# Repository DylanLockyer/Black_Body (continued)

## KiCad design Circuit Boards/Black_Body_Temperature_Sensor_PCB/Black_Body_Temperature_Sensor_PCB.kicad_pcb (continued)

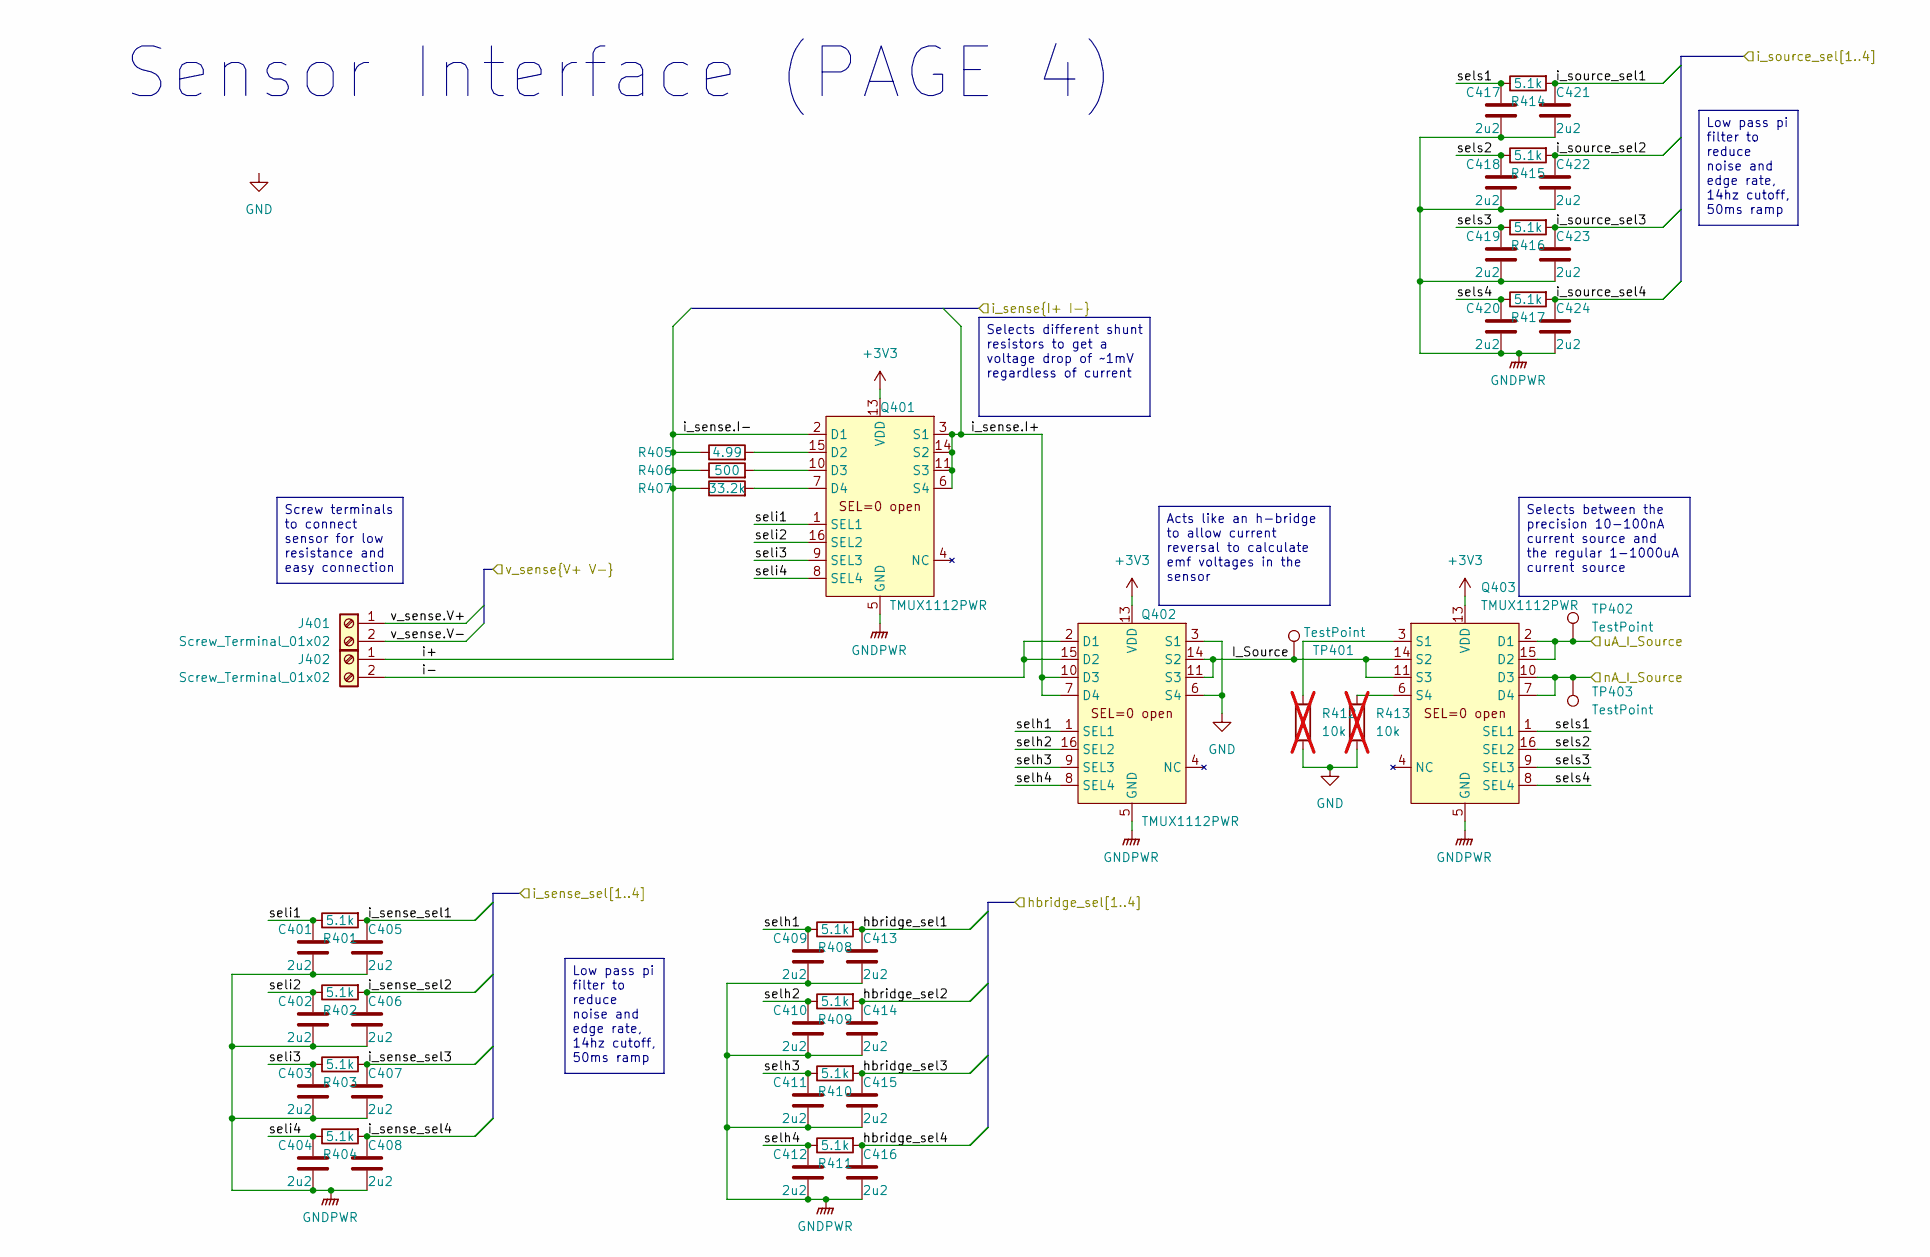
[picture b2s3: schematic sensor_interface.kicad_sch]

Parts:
C401, C402, C403, C404, C405, C406, C407, C408, C409, C410, C411, C412, C413, C414, C415, C416, C417, C418, C419, C420, C421, C422, C423, C424: 2u2; C_0402_1005Metric; MPN GRM155R61E225ME15D
J401, J402: Screw_Terminal_01x02; CUI_TB002-500-02BE; MPN TB002-500-02BE
Q401, Q402, Q403: TMUX1112PWR; TSSOP-16_4.4x5mm_P0.65mm; MPN TMUX1112PWR
R401, R402, R403, R404, R408, R409, R410, R411, R414, R415, R416, R417: 5.1k; R_0402_1005Metric; MPN RT0402BRD075K1L
R405: 4.99; R_0603_1608Metric; MPN RN73C1J4R99BTD
R406: 500; R_0603_1608Metric; MPN ERA-3AEB4990V
R407: 33.2k; R_0603_1608Metric; MPN ERA-3AEB3322V
R412, R413: 10k; R_0603_1608Metric; MPN ERA-3AEB103V; not fitted
TP401, TP402, TP403: TestPoint; TestPoint_Pad_2.0x2.0mm

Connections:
+3V3: Q401.13 (VDD), Q402.13 (VDD), Q403.13 (VDD); also elsewhere on the board
/V&I_sense/i_sense.I+: Q401.3 (S1), Q401.6 (S4), Q401.11 (S3), Q401.14 (S2), Q402.7 (D4), Q402.10 (D3); also elsewhere on the board
/V&I_sense/i_sense.I-: J402.1, Q401.2 (D1), R405.1, R406.1, R407.1; also elsewhere on the board
/V&I_sense/v_sense.V+: J401.1; also elsewhere on the board
/V&I_sense/v_sense.V-: J401.2; also elsewhere on the board
/micrcontroller/hbridge_sel1: C413.1, R408.2; also elsewhere on the board
/micrcontroller/hbridge_sel2: C414.1, R409.2; also elsewhere on the board
/micrcontroller/hbridge_sel3: C415.1, R410.2; also elsewhere on the board
/micrcontroller/hbridge_sel4: C416.1, R411.2; also elsewhere on the board
/micrcontroller/i_sense_sel1: C405.1, R401.2; also elsewhere on the board
/micrcontroller/i_sense_sel2: C406.1, R402.2; also elsewhere on the board
/micrcontroller/i_sense_sel3: C407.1, R403.2; also elsewhere on the board
/micrcontroller/i_sense_sel4: C408.1, R404.2; also elsewhere on the board
/micrcontroller/i_source_sel1: C421.1, R414.2; also elsewhere on the board
/micrcontroller/i_source_sel2: C422.1, R415.2; also elsewhere on the board
/micrcontroller/i_source_sel3: C423.1, R416.2; also elsewhere on the board
/micrcontroller/i_source_sel4: C424.1, R417.2; also elsewhere on the board
/nA_current/nA_I_Source: Q403.7 (D4), Q403.10 (D3), TP403.1 (1_1); also elsewhere on the board
/sensor_interface/I_Source: Q402.11 (S3), Q402.14 (S2), Q403.11 (S3), Q403.14 (S2), TP401.1 (1_1)
/sensor_interface/i-: J402.2, Q402.2 (D1), Q402.15 (D2)
/sensor_interface/selh1: C409.1, Q402.1 (SEL1), R408.1
/sensor_interface/selh2: C410.1, Q402.16 (SEL2), R409.1
/sensor_interface/selh3: C411.1, Q402.9 (SEL3), R410.1
/sensor_interface/selh4: C412.1, Q402.8 (SEL4), R411.1
/sensor_interface/seli1: C401.1, Q401.1 (SEL1), R401.1
/sensor_interface/seli2: C402.1, Q401.16 (SEL2), R402.1
/sensor_interface/seli3: C403.1, Q401.9 (SEL3), R403.1
/sensor_interface/seli4: C404.1, Q401.8 (SEL4), R404.1
/sensor_interface/sels1: C417.1, Q403.1 (SEL1), R414.1
/sensor_interface/sels2: C418.1, Q403.16 (SEL2), R415.1
/sensor_interface/sels3: C419.1, Q403.9 (SEL3), R416.1
/sensor_interface/sels4: C420.1, Q403.8 (SEL4), R417.1
/sensor_interface/uA_I_Source: Q403.2 (D1), Q403.15 (D2), TP402.1 (1_1); also elsewhere on the board
GND: Q402.3 (S1), Q402.6 (S4), R412.2, R413.2; also elsewhere on the board
GNDPWR: C401.2, C402.2, C403.2, C404.2, C405.2, C406.2, C407.2, C408.2, C409.2, C410.2, C411.2, C412.2, C413.2, C414.2, C415.2, C416.2, C417.2, C418.2, C419.2, C420.2, C421.2, C422.2, C423.2, C424.2, Q401.5 (GND), Q402.5 (GND), Q403.5 (GND); also elsewhere on the board
unnamed: Q401.15 (D2), R405.2
unnamed: Q401.10 (D3), R406.2
unnamed: Q401.7 (D4), R407.2
unnamed: Q403.3 (S1), R412.1
unnamed: Q403.6 (S4), R413.1

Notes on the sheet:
Sensor Interface (PAGE 4)
Low pass pi filter to reduce noise and edge rate, 14hz cutoff, 50ms ramp
Acts like an h-bridge to allow current reversal to calculate emf voltages in the sensor
Selects different shunt resistors to get a voltage drop of ~1mV regardless of current
Screw terminals to connect sensor for low resistance and easy connection
Selects between the precision 10-100nA current source and the regular 1-1000uA current source

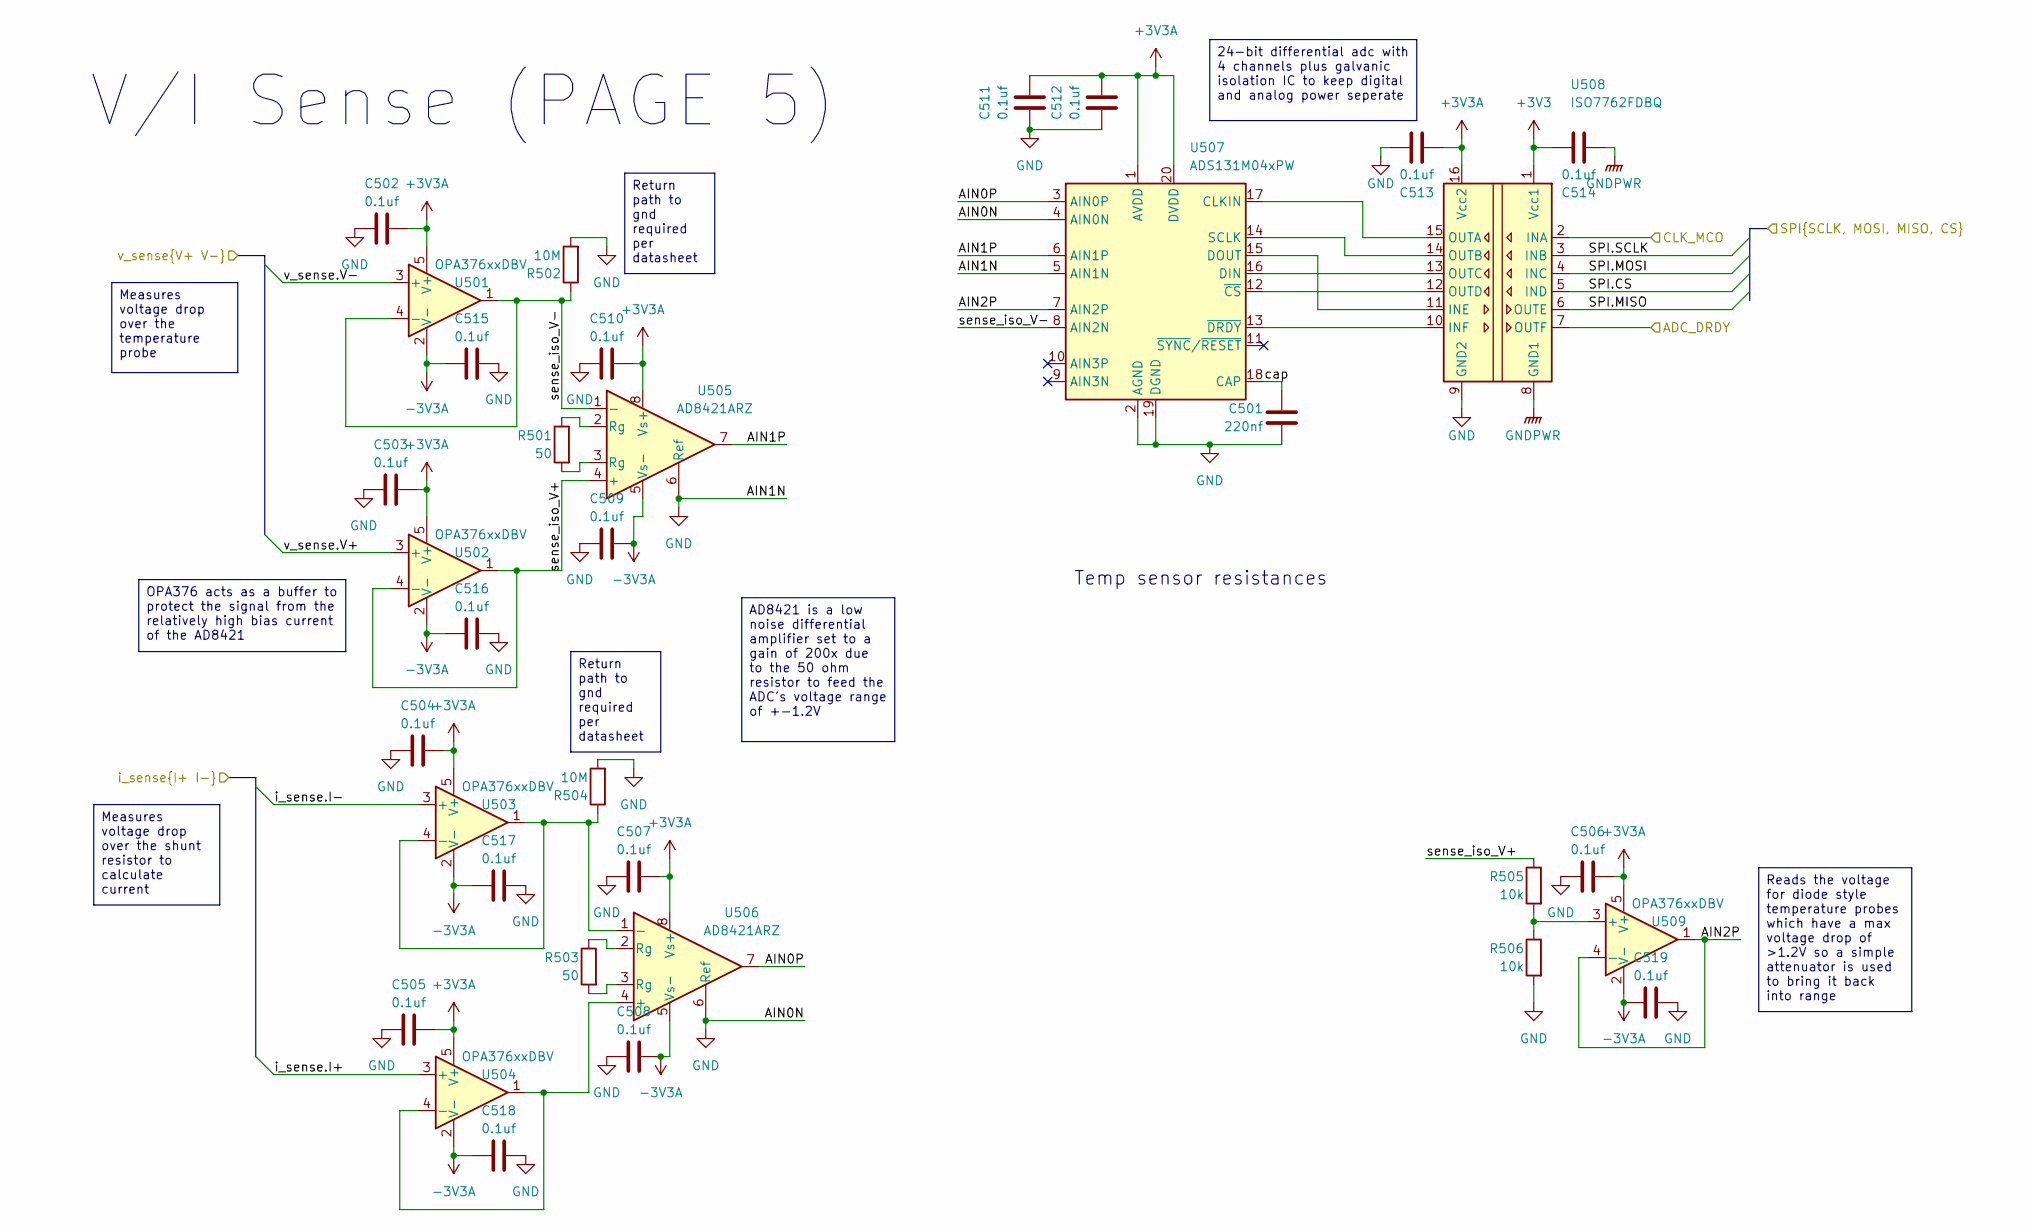
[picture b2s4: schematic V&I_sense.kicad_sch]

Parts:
C501: 220nf; C_0603_1608Metric; MPN GCM188R71H224KA64D
C502, C503, C504, C505, C506, C507, C508, C509, C510, C511, C512, C513, C514, C515, C516, C517, C518, C519: 0.1uf; C_0603_1608Metric; MPN CL10B104KB8NNNC
R501, R503: 50; R_0603_1608Metric; MPN ERA-3AEB49R9V
R502, R504: 10M; R_0603_1608Metric; MPN CRCW060310M0DHEAP
R505, R506: 10k; R_0603_1608Metric; MPN ERA-3AEB103V
U501, U502, U503, U504, U509: OPA376xxDBV; SOT-23-5; MPN OPA376AIDBVR
U505, U506: AD8421ARZ; SOIC-8_3.9x4.9mm_P1.27mm; MPN AD8421ARZ
U507: ADS131M04xPW; TSSOP-20_4.4x6.5mm_P0.65mm; MPN ADS131M04IPWR
U508: ISO7762FDBQ; SSOP-16_3.9x4.9mm_P0.635mm; MPN ISO7762FDBQ

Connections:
+3V3: C514.2, U508.1 (Vcc1); also elsewhere on the board
+3V3A: C502.1, C503.1, C504.1, C505.1, C506.1, C507.1, C510.1, C511.1, C512.1, C513.2, U501.5 (V+), U502.5 (V+), U503.5 (V+), U504.5 (V+), U505.8 (Vs+), U506.8 (Vs+), U507.1 (AVDD), U507.20 (DVDD), U508.16 (Vcc2), U509.5 (V+); also elsewhere on the board
-3V3A: C508.1, C509.1, C515.1, C516.1, C517.1, C518.1, C519.1, U501.2 (V-), U502.2 (V-), U503.2 (V-), U504.2 (V-), U505.5 (Vs-), U506.5 (Vs-), U509.2 (V-); also elsewhere on the board
/V&I_sense/ADC_DRDY: U508.7 (OUTF); also elsewhere on the board
/V&I_sense/AIN0P: U506.7, U507.3 (AIN0P)
/V&I_sense/AIN1P: U505.7, U507.6 (AIN1P)
/V&I_sense/AIN2P: U507.7 (AIN2P), U509.1, U509.4 (-)
/V&I_sense/CLK_MCO: U508.2 (INA); also elsewhere on the board
/V&I_sense/SPI.CS: U508.5 (IND); also elsewhere on the board
/V&I_sense/SPI.MISO: U508.6 (OUTE); also elsewhere on the board
/V&I_sense/SPI.MOSI: U508.4 (INC); also elsewhere on the board
/V&I_sense/SPI.SCLK: U508.3 (INB); also elsewhere on the board
/V&I_sense/cap: C501.1, U507.18 (CAP)
/V&I_sense/i_sense.I+: U504.3 (+); also elsewhere on the board
/V&I_sense/i_sense.I-: U503.3 (+); also elsewhere on the board
/V&I_sense/sense_iso_V+: R505.1, U502.1, U502.4 (-), U505.4 (+)
/V&I_sense/sense_iso_V-: R502.1, U501.1, U501.4 (-), U505.1 (-), U507.8 (AIN2N)
/V&I_sense/v_sense.V+: U502.3 (+); also elsewhere on the board
/V&I_sense/v_sense.V-: U501.3 (+); also elsewhere on the board
GND: C501.2, C502.2, C503.2, C504.2, C505.2, C506.2, C507.2, C508.2, C509.2, C510.2, C511.2, C512.2, C513.1, C515.2, C516.2, C517.2, C518.2, C519.2, R502.2, R504.2, R506.2, U505.6 (Ref), U506.6 (Ref), U507.2 (AGND), U507.4 (AIN0N), U507.5 (AIN1N), U507.19 (DGND), U508.9 (GND2); also elsewhere on the board
GNDPWR: C514.1, U508.8 (GND1); also elsewhere on the board
unnamed: R501.1, U505.2 (Rg)
unnamed: R501.2, U505.3 (Rg)
unnamed: R503.1, U506.2 (Rg)
unnamed: R503.2, U506.3 (Rg)
unnamed: R504.1, U503.1, U503.4 (-), U506.1 (-)
unnamed: U504.1, U504.4 (-), U506.4 (+)
unnamed: U507.17 (CLKIN), U508.15 (OUTA)
unnamed: U507.16 (DIN), U508.13 (OUTC)
unnamed: U507.15 (DOUT), U508.11 (INE)
unnamed: U507.14 (SCLK), U508.14 (OUTB)
unnamed: U507.12 (~CS), U508.12 (OUTD)
unnamed: U507.13 (~DRDY), U508.10 (INF)
unnamed: R505.2, R506.1, U509.3 (+)

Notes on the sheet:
Temp sensor resistances
V/I Sense (PAGE 5)
Return path to gnd required per datasheet
Measures voltage drop over the temperature probe
Measures voltage drop over the shunt resistor to calculate current
Reads the voltage for diode style temperature probes which have a max voltage drop of >1.2V so a simple attenuator is used to bring it back into range
OPA376 acts as a buffer to protect the signal from the relatively high bias current of the AD8421
AD8421 is a low noise differential amplifier set to a gain of 200x due to the 50 ohm resistor to feed the ADC's voltage range of +-1.2V
24-bit differential adc with 4 channels plus galvanic isolation IC to keep digital and analog power seperate

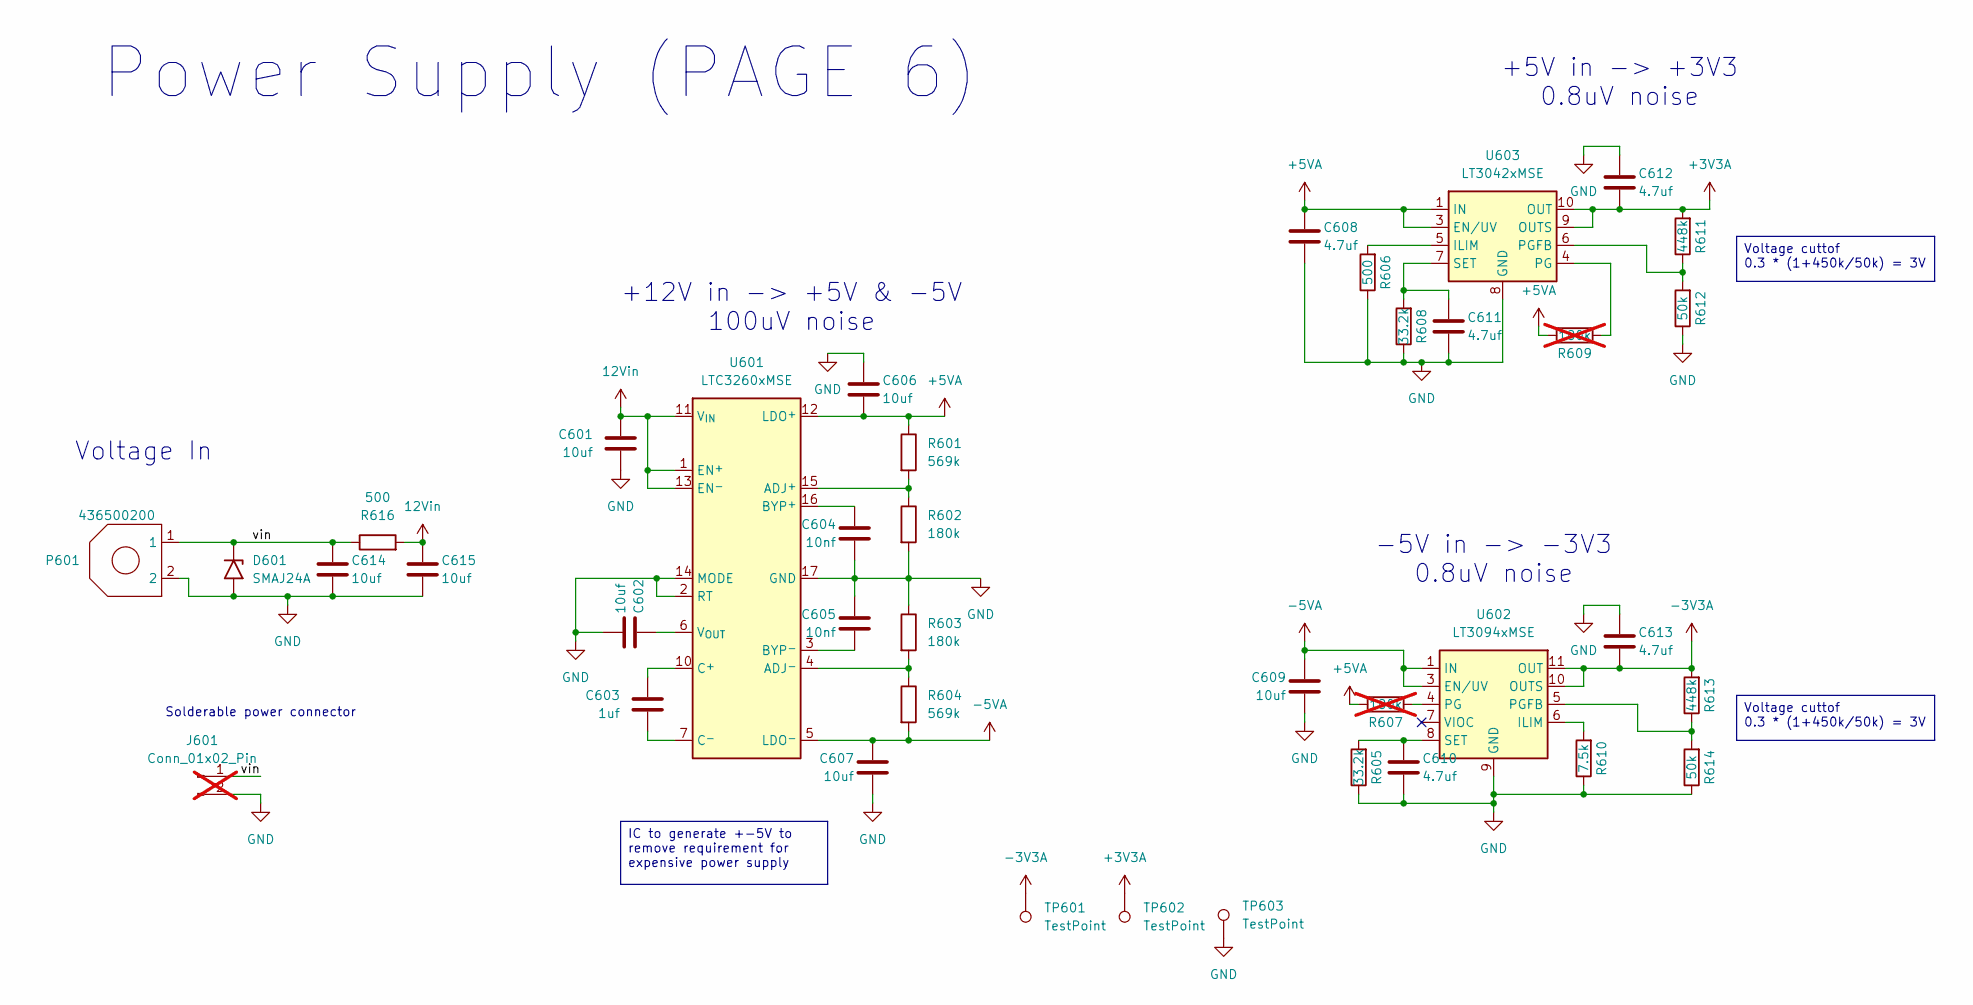
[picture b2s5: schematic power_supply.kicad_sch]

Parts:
C601, C602, C606, C607, C609, C614, C615: 10uf; C_0603_1608Metric; MPN GRM188R6YA106MA73D
C603: 1uf; C_0603_1608Metric; MPN C0603C105K4RACTU
C604, C605: 10nf; C_0603_1608Metric; MPN CL10B103KB8NNNC
C608, C610, C611, C612, C613: 4.7uf; C_0603_1608Metric; MPN CL10A475KO8NNNC
D601: SMAJ24A; D_SMA; MPN SMAJ24A
J601: Conn_01x02_Pin; PinHeader_1x02_P2.54mm_Vertical; not fitted
P601: 436500200; 436500200 2-pin; MPN 436500200
R601, R604: 569k; R_0603_1608Metric; MPN RN73H1JTTD5693B50
R602, R603: 180k; R_0603_1608Metric; MPN ERA-3AEB184V
R605, R608: 33.2k; R_0603_1608Metric; MPN ERA-3AEB3322V
R606, R616: 500; R_0603_1608Metric; MPN ERA-3AEB4990V
R607, R609: 180k; R_0603_1608Metric; MPN ERA-3AEB184V; not fitted
R610: 7.5k; R_0603_1608Metric; MPN ERA-3AEB752V
R611, R613: 448k; R_0603_1608Metric; MPN RT0603BRD07448KL
R612, R614: 50k; R_0603_1608Metric; MPN RT0603BRD0750KL
TP601, TP602, TP603: TestPoint; TestPoint_Pad_2.0x2.0mm
U601: LTC3260xMSE; MSOP-16-1EP_3x4.039mm_P0.5mm_EP1.651x2.845mm; MPN LTC3260EMSE#TRPBF
U602: LT3094xMSE; MSOP-12-1EP_3x4.039mm_P0.65mm_EP1.651x2.845mm; MPN LT3094EMSE#TRPBF
U603: LT3042xMSE; MSOP-10-1EP_3x3mm_P0.5mm_EP1.68x1.88mm; MPN LT3042EMSE#TRPBF

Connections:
12Vin: C601.1, C615.1, R616.2, U601.1 (EN^{+}), U601.11 (V_{IN}), U601.13 (EN^{-})
+3V3A: C612.2, R611.2, TP602.1 (1_1), U603.9 (OUTS), U603.10 (OUT); also elsewhere on the board
+5VA: C606.2, C608.1, R601.1, R607.2, R609.2, U601.12 (LDO^{+}), U603.1 (IN), U603.2 (IN), U603.3 (EN/UV)
-3V3A: C613.2, R613.2, TP601.1 (1_1), U602.10 (OUTS), U602.11 (OUT), U602.12 (OUT); also elsewhere on the board
-5VA: C607.1, C609.1, R604.2, U601.5 (LDO^{-}), U602.1 (IN), U602.2 (IN), U602.3 (EN/UV), U602.13 (IN)
/power_supply/vin: C614.1, D601.1 (A1), J601.1, P601.1, R616.1
GND: C601.2, C602.2, C604.2, C605.1, C606.1, C607.2, C608.2, C609.2, C610.2, C611.2, C612.1, C613.1, C614.2, C615.2, D601.2 (A2), J601.2, P601.2, R602.2, R603.1, R605.1, R606.1, R608.1, R610.1, R612.1, R614.1, TP603.1 (1_1), U601.2 (RT), U601.14 (MODE), U601.17 (GND), U602.9 (GND), U603.8 (GND), U603.11 (GND); also elsewhere on the board
unnamed: R601.2, R602.1, U601.15 (ADJ^{+})
unnamed: R603.2, R604.1, U601.4 (ADJ^{-})
unnamed: C604.1, U601.16 (BYP^{+})
unnamed: C605.2, U601.3 (BYP^{-})
unnamed: C603.1, U601.10 (C^{+})
unnamed: C603.2, U601.7 (C^{-})
unnamed: C602.1, U601.6 (V_{OUT})
unnamed: R610.2, U602.6 (ILIM)
unnamed: R607.1, U602.4 (PG)
unnamed: R613.1, R614.2, U602.5 (PGFB)
unnamed: C610.1, R605.2, U602.8 (SET)
unnamed: R606.2, U603.5 (ILIM)
unnamed: R609.1, U603.4 (PG)
unnamed: R611.1, R612.2, U603.6 (PGFB)
unnamed: C611.1, R608.2, U603.7 (SET)

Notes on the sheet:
+5V in -> +3V3 0.8uV noise
Voltage In
Power Supply (PAGE 6)
+12V in -> +5V & -5V 100uV noise
Solderable power connector
-5V in -> -3V3 0.8uV noise
Voltage cuttof 0.3 * (1+450k/50k) = 3V
IC to generate +-5V to remove requirement for expensive power supply

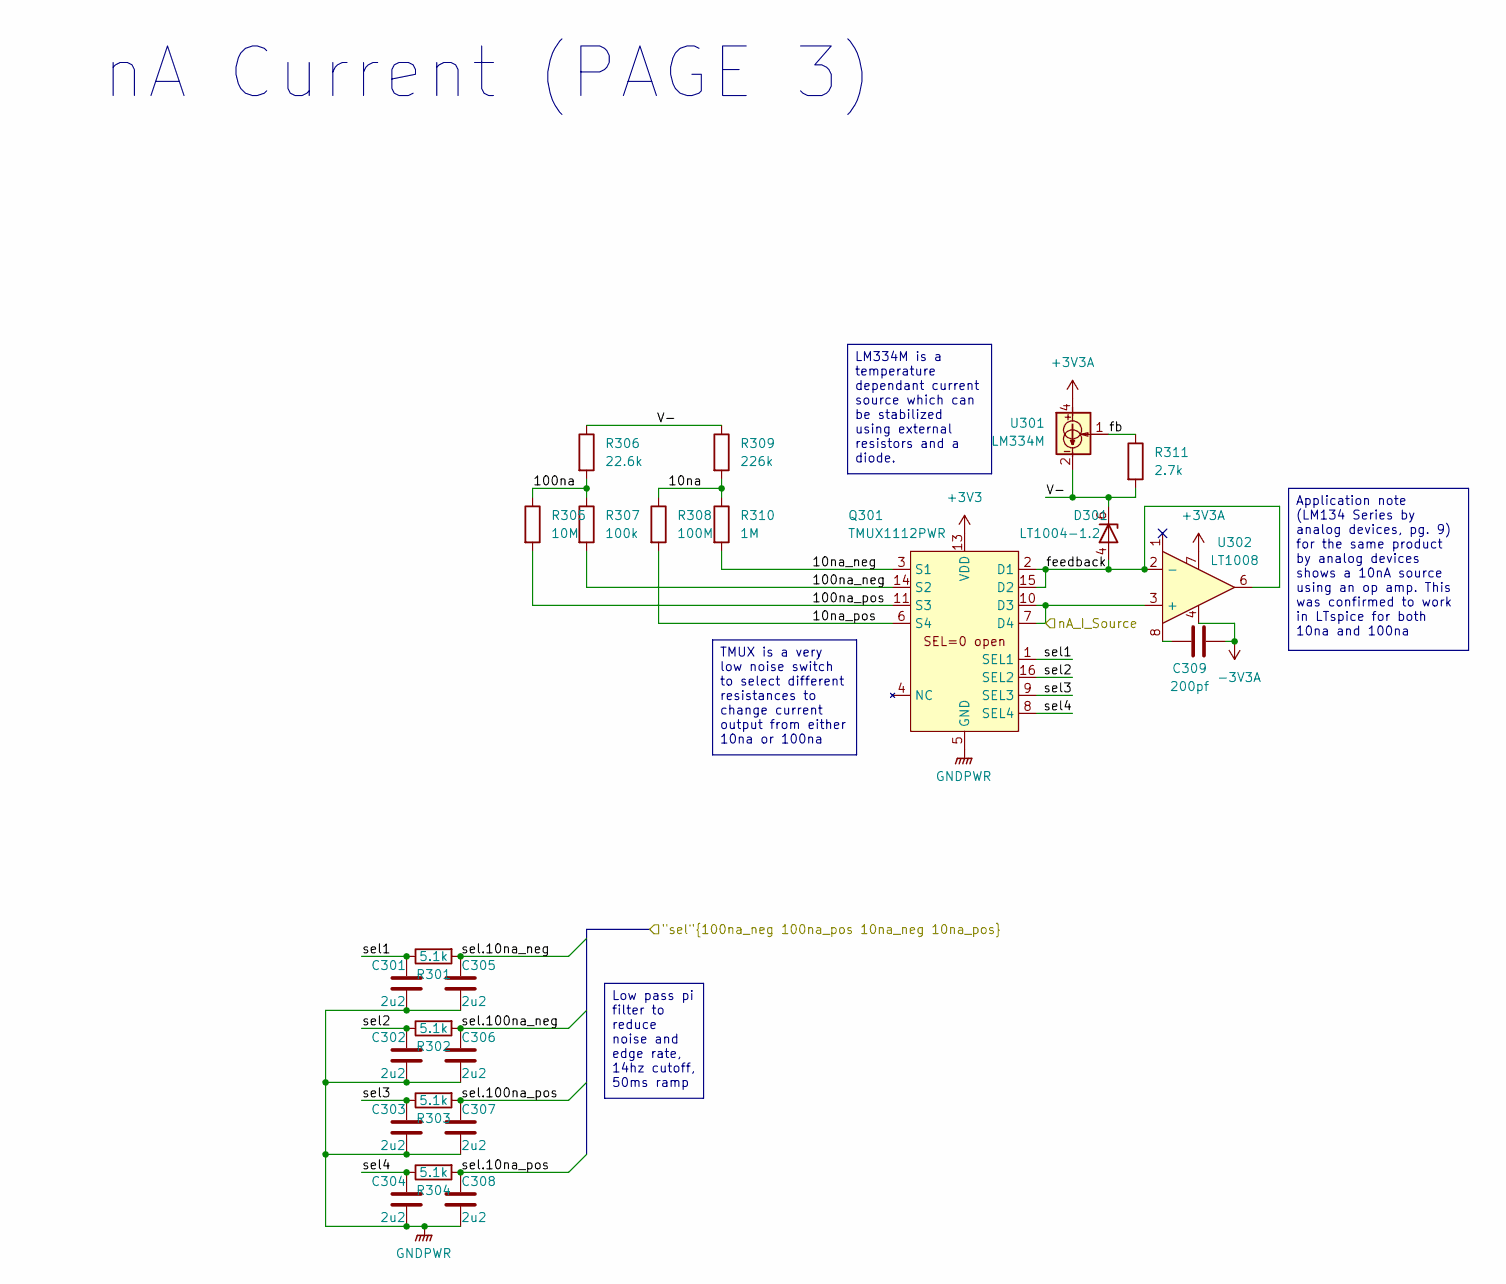
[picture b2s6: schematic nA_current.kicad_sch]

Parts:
C301, C302, C303, C304, C305, C306, C307, C308: 2u2; C_0402_1005Metric; MPN GRM155R61E225ME15D
C309: 200pf; C_0603_1608Metric; MPN CL10C201JB8NNNC
D301: LT1004-1.2; SOIC-8_3.9x4.9mm_P1.27mm; MPN LT1004CS8-1.2#TRPBF
Q301: TMUX1112PWR; TSSOP-16_4.4x5mm_P0.65mm; MPN TMUX1112PWR
R301, R302, R303, R304: 5.1k; R_0402_1005Metric; MPN RT0402BRD075K1L
R305: 10M; R_0603_1608Metric; MPN CRCW060310M0DHEAP
R306: 22.6k; R_0603_1608Metric; MPN ERA-3AEB2262V
R307: 100k; R_0603_1608Metric; MPN ERA-3AEB104V
R308: 100M; R_0603_1608Metric; MPN HVC0603T1006FET
R309: 226k; R_0603_1608Metric; MPN ERA-3AEB2263V
R310: 1M; R_0603_1608Metric; MPN RN73H1JTTD1004B25
R311: 2.7k; R_0603_1608Metric; MPN ERA-3AEB272V
U301: LM334M; SOIC-8_3.9x4.9mm_P1.27mm; MPN LM334M
U302: LT1008; SOIC-8_3.9x4.9mm_P1.27mm; MPN LT1008S8#PBF

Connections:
+3V3: Q301.13 (VDD); also elsewhere on the board
+3V3A: U301.4, U302.7; also elsewhere on the board
-3V3A: C309.2, U302.4; also elsewhere on the board
/micrcontroller/sel.10na_neg: C305.1, R301.2; also elsewhere on the board
/micrcontroller/sel.10na_pos: C308.1, R304.2; also elsewhere on the board
/micrcontroller/sel.100na_neg: C306.1, R302.2; also elsewhere on the board
/micrcontroller/sel.100na_pos: C307.1, R303.2; also elsewhere on the board
/nA_current/10na: R308.1, R309.2, R310.1
/nA_current/10na_neg: Q301.3 (S1), R310.2
/nA_current/10na_pos: Q301.6 (S4), R308.2
/nA_current/100na: R305.1, R306.2, R307.1
/nA_current/100na_neg: Q301.14 (S2), R307.2
/nA_current/100na_pos: Q301.11 (S3), R305.2
/nA_current/V-: D301.6, D301.8, R306.1, R309.1, R311.2, U301.2, U301.3, U301.6, U301.7
/nA_current/fb: R311.1, U301.1
/nA_current/feedback: D301.4, Q301.2 (D1), Q301.15 (D2), U302.2 (-), U302.6
/nA_current/nA_I_Source: Q301.7 (D4), Q301.10 (D3), U302.3 (+); also elsewhere on the board
/nA_current/sel1: C301.1, Q301.1 (SEL1), R301.1
/nA_current/sel2: C302.1, Q301.16 (SEL2), R302.1
/nA_current/sel3: C303.1, Q301.9 (SEL3), R303.1
/nA_current/sel4: C304.1, Q301.8 (SEL4), R304.1
GNDPWR: C301.2, C302.2, C303.2, C304.2, C305.2, C306.2, C307.2, C308.2, Q301.5 (GND); also elsewhere on the board
unnamed: C309.1, U302.8

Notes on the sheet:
nA Current (PAGE 3)
Application note (LM134 Series by analog devices, pg. 9) for the same product by analog devices shows a 10nA source using an op amp. This was confirmed to work in LTspice for both 10na and 100na
LM334M is a temperature dependant current source which can be stabilized using external resistors and a diode.
TMUX is a very low noise switch to select different resistances to change current output from either 10na or 100na
Low pass pi filter to reduce noise and edge rate, 14hz cutoff, 50ms ramp

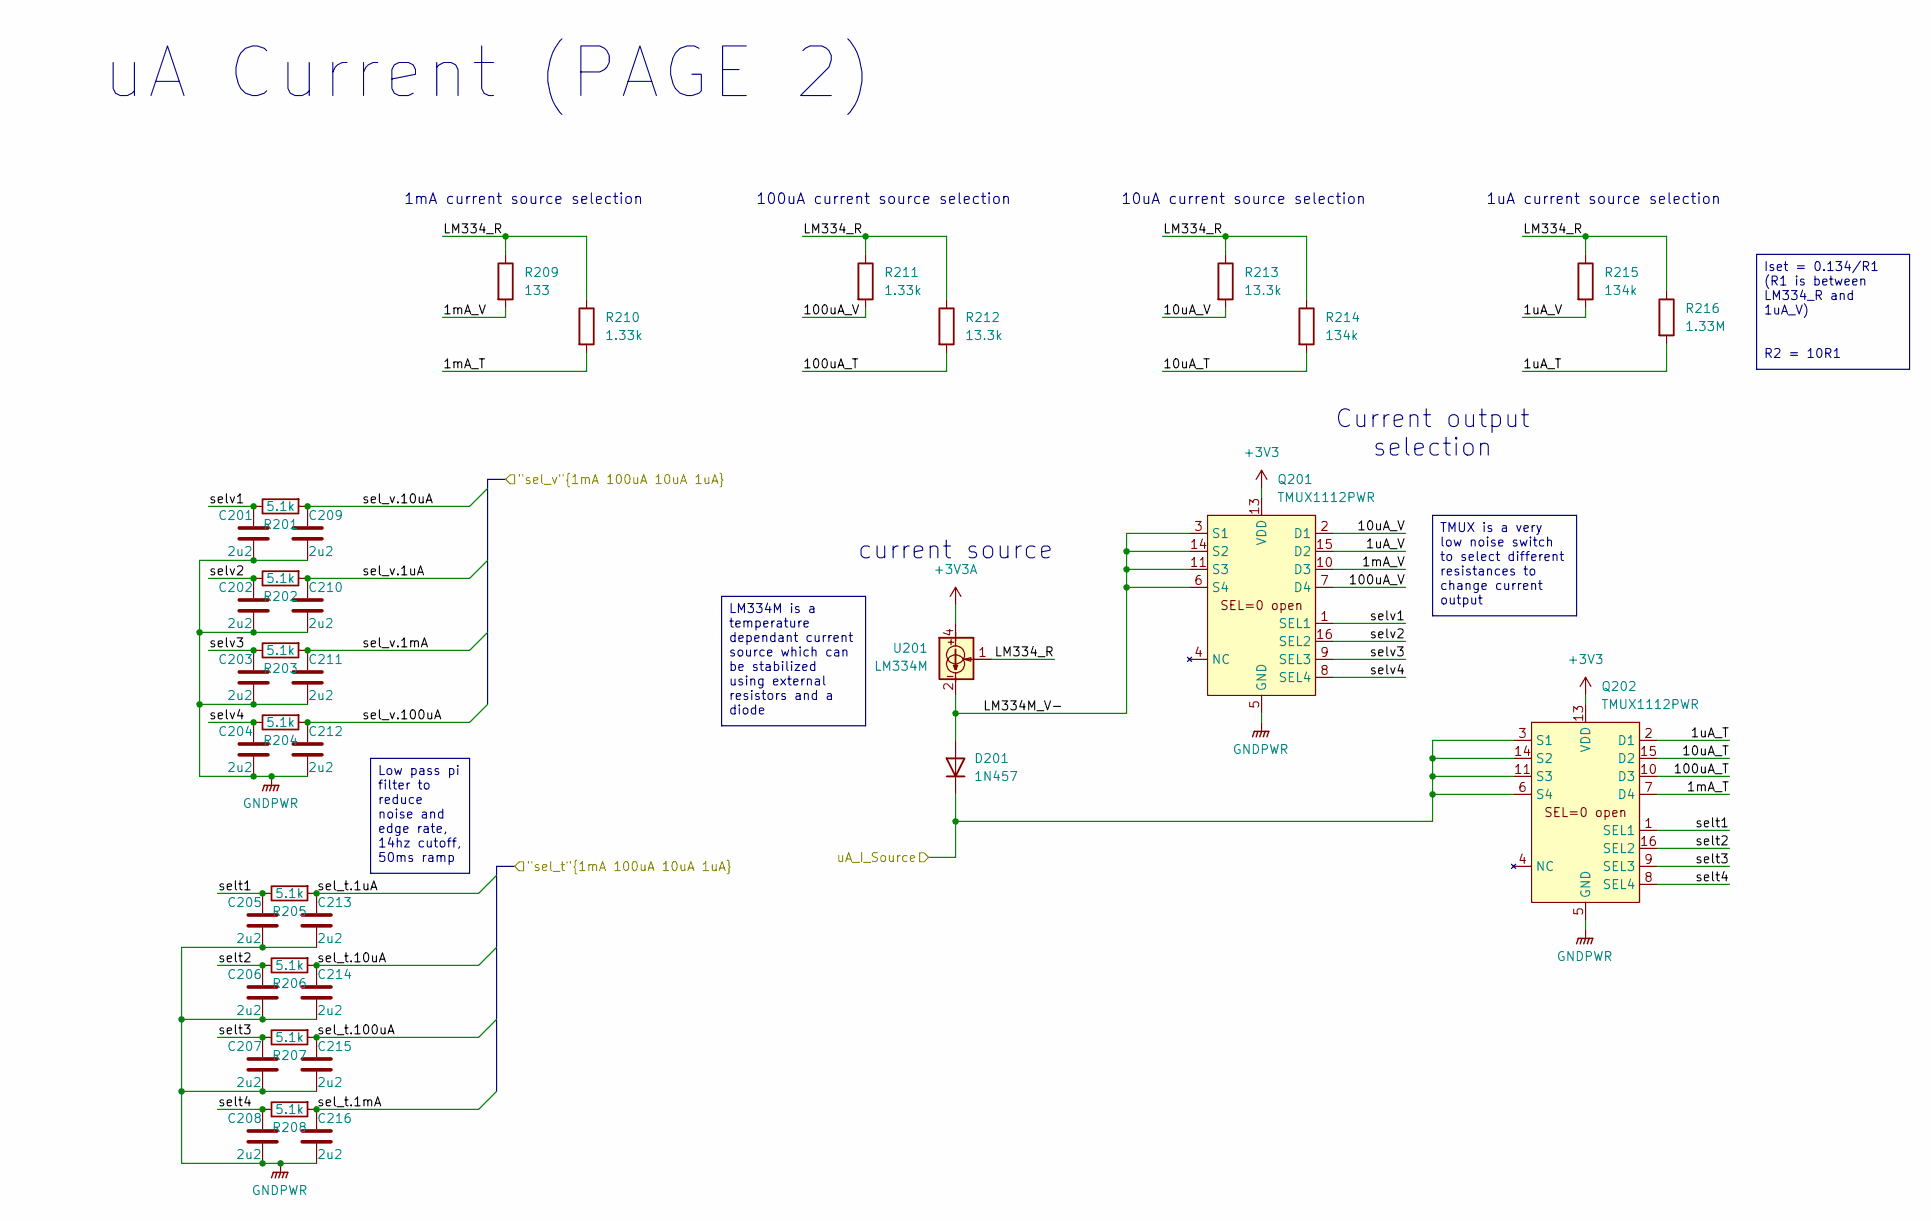
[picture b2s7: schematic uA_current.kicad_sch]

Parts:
C201, C202, C203, C204, C205, C206, C207, C208, C209, C210, C211, C212, C213, C214, C215, C216: 2u2; C_0402_1005Metric; MPN GRM155R61E225ME15D
D201: 1N457; D_DO-35_SOD27_P7.62mm_Horizontal; MPN 1N457
Q201, Q202: TMUX1112PWR; TSSOP-16_4.4x5mm_P0.65mm; MPN TMUX1112PWR
R201, R202, R203, R204, R205, R206, R207, R208: 5.1k; R_0402_1005Metric; MPN RT0402BRD075K1L
R209: 133; R_0603_1608Metric; MPN RQ73C1J133RBTD
R210, R211: 1.33k; R_0603_1608Metric; MPN ERA-3AEB1331V
R212, R213: 13.3k; R_0603_1608Metric; MPN ERA-3AEB1332V
R214, R215: 134k; R_0603_1608Metric; MPN ERA-3AEB1333V
R216: 1.33M; R_0603_1608Metric; MPN RK73H1JTTD1334F
U201: LM334M; SOIC-8_3.9x4.9mm_P1.27mm; MPN LM334M

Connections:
+3V3: Q201.13 (VDD), Q202.13 (VDD); also elsewhere on the board
+3V3A: U201.4; also elsewhere on the board
/micrcontroller/sel_t.1mA: C216.1, R208.2; also elsewhere on the board
/micrcontroller/sel_t.1uA: C213.1, R205.2; also elsewhere on the board
/micrcontroller/sel_t.10uA: C214.1, R206.2; also elsewhere on the board
/micrcontroller/sel_t.100uA: C215.1, R207.2; also elsewhere on the board
/micrcontroller/sel_v.1mA: C211.1, R203.2; also elsewhere on the board
/micrcontroller/sel_v.1uA: C210.1, R202.2; also elsewhere on the board
/micrcontroller/sel_v.10uA: C209.1, R201.2; also elsewhere on the board
/micrcontroller/sel_v.100uA: C212.1, R204.2; also elsewhere on the board
/sensor_interface/uA_I_Source: D201.1 (K), Q202.3 (S1), Q202.6 (S4), Q202.11 (S3), Q202.14 (S2); also elsewhere on the board
/uA_current/1mA_T: Q202.7 (D4), R210.2
/uA_current/1mA_V: Q201.10 (D3), R209.2
/uA_current/1uA_T: Q202.2 (D1), R216.2
/uA_current/1uA_V: Q201.15 (D2), R215.2
/uA_current/10uA_T: Q202.15 (D2), R214.2
/uA_current/10uA_V: Q201.2 (D1), R213.2
/uA_current/100uA_T: Q202.10 (D3), R212.2
/uA_current/100uA_V: Q201.7 (D4), R211.2
/uA_current/LM334M_V-: D201.2 (A), Q201.3 (S1), Q201.6 (S4), Q201.11 (S3), Q201.14 (S2), U201.2, U201.3, U201.6, U201.7
/uA_current/LM334_R: R209.1, R210.1, R211.1, R212.1, R213.1, R214.1, R215.1, R216.1, U201.1
/uA_current/selt1: C205.1, Q202.1 (SEL1), R205.1
/uA_current/selt2: C206.1, Q202.16 (SEL2), R206.1
/uA_current/selt3: C207.1, Q202.9 (SEL3), R207.1
/uA_current/selt4: C208.1, Q202.8 (SEL4), R208.1
/uA_current/selv1: C201.1, Q201.1 (SEL1), R201.1
/uA_current/selv2: C202.1, Q201.16 (SEL2), R202.1
/uA_current/selv3: C203.1, Q201.9 (SEL3), R203.1
/uA_current/selv4: C204.1, Q201.8 (SEL4), R204.1
GNDPWR: C201.2, C202.2, C203.2, C204.2, C205.2, C206.2, C207.2, C208.2, C209.2, C210.2, C211.2, C212.2, C213.2, C214.2, C215.2, C216.2, Q201.5 (GND), Q202.5 (GND); also elsewhere on the board

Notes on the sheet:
current source
Current output selection
uA Current (PAGE 2)
100uA current source selection
10uA current source selection
1mA current source selection
1uA current source selection
LM334M is a temperature dependant current source which can be stabilized using external resistors and a diode
Iset = 0.134/R1 (R1 is between LM334_R and 1uA_V) R2 = 10R1
Low pass pi filter to reduce noise and edge rate, 14hz cutoff, 50ms ramp
TMUX is a very low noise switch to select different resistances to change current output
